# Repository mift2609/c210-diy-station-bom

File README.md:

# Checklist Belanja — Station Solder C210 DIY

Halaman checklist komponen untuk membangun station solder C210 (kartrid JBC C210) berbasis
Arduino Nano / ATmega328P + LMV358, ditujukan untuk service HP dan elektronik kecil.

- `index.html` — checklist interaktif: centang per komponen, harga bisa diedit, total otomatis,
  tombol salin daftar yang belum dibeli, dan link pencarian Shopee per komponen.
- `c210-station-belanja-uji.xlsx` — versi spreadsheet: daftar belanja, daftar upgrade,
  item off-PCB/gagang DIY, checklist uji terima, dan tabel kalibrasi suhu.
- `checklist.html` (kalau ada) — versi tanpa data harga Shopee.

## Estimasi biaya

| Bagian | Biaya |
|---|---|
| Komponen PCB wajib (otak + SMD + THT) | Rp159.500 |
| Off-PCB & gagang DIY (fab PCB, tip, soket, kabel, PSU, stand, enclosure) | Rp345.000 – Rp830.000 |
| Upgrade elektronik opsional (OPA2387, buck 5V, MOSFET ≥40V, earth tip, snubber) | +Rp87.000 |
| **Total** | **Rp504.500 – Rp989.500** (dengan upgrade: Rp587.500 – Rp1.072.500) |

## Varian gagang & rail (15 Nov 2026)

Satu board, satu colokan, gantian gagang:

- **C210 (12 V)** — rail dasar, kartrid ~2 ohm.
- **T210 / gagang 12 V** — lihat [`09-gantian-gagang.md`](09-gantian-gagang.md):
  autodetect gagang lewat ID pin (D10), 2 slot tip, firmware `firmware-gantian/`
  (v1.3-C210g, 24.412 byte).
- **T12 (24 V)** — lihat [`12-dual-rail-c210-t12.md`](12-dual-rail-c210-t12.md):
  PSU 36 V (terukur) -> buck 24 V (T12) + buck 12 V (C210) (buck input >= 50 V), dipilih **relay SPDT** yang
  dikendalikan D2; rail ikut profil tip otomatis. Firmware `firmware-dualrail/`
  (v1.3-dual, 24.570 byte). Wajib untuk rail 24 V: MOSFET >= 40 V, 5 V dari buck,
  sekring ikut R kartrid.

Tabel daya tip: C210 ~2 ohm -> 12 V = 72 W (24 V = 288 W, jangan);
T12 ~8 ohm -> 12 V = 18 W, 24 V = 72 W.

## Angka sekring & PSU: ukur R kartrid dulu

Doc lama memakai 8,5 ohm / ~1,4 A (angka tip T12). Rumus: `I = 12 / R`.

| R kartrid | Arus puncak @12 V | Sekring | PSU/rail |
|---|---|---|---|
| ~2 ohm (C210) | ~6,0 A | 8 A | >=8 A |
| ~2,5-3 ohm | ~4,0-4,8 A | 6,3-8 A | >=6 A |
| ~8 ohm (T12) | ~1,5 A | 3 A fast | >=3 A (lemah di 12 V) |

## Sebelum dipakai menyolder board HP

1. PSU harus **SELV/floating** — jangan pakai adaptor atau charger yang outputnya terhubung ke earth.
2. Sambungkan **kabel earth dari soket kartrid ke chassis** lalu ke PE. Ukur: tip-ke-earth < 2 Ω, kebocoran < 2 mV.
3. Kalibrasi suhu di 250/300/350 °C dengan thermocouple meter — target error < ±20 °C.
4. Uji fail-safe: cabut kartrid / satu kabel termokopel saat heater ON, daya harus terputus.
5. Kalau OPA2387 dipasang menggantikan LMV358, kalibrasi wajib diulang.

Catatan: seluruh angka harga adalah estimasi snapshot dan perlu dicek ulang saat membeli.

## Catatan gerber (penting)

File gerber asli yang beredar untuk board ini punya **cacat ekspor**: layer solder
mask (`F_Mask`/`B_Mask`) hanya memuat 56 bukaan untuk pad through-hole dan mounting
hole, sedangkan **pad SMD tidak punya bukaan sama sekali** (F_Cu punya 209 pad,
F_Mask hanya 56 objek; pad SMD terlihat tertutup mask pada render). Preview desainer
sendiri menunjukkan pad SMD terbuka, jadi ini murni cacat ekspor, bukan salah desain.

Kalau diorder apa adanya, pad SMD akan tertutup solder mask dan tidak bisa disolder.
Dua jalan keluar: minta desainer ekspor ulang gerber, atau pakai versi perbaikan
(mask di-generate ulang dari copper: bukaan THT dipertahankan + bukaan pad SMD
ditambahkan dengan ekspansi 0,1 mm, via tetap tertutup).

## Live

Checklist interaktif: https://mift2609.github.io/c210-diy-station-bom/

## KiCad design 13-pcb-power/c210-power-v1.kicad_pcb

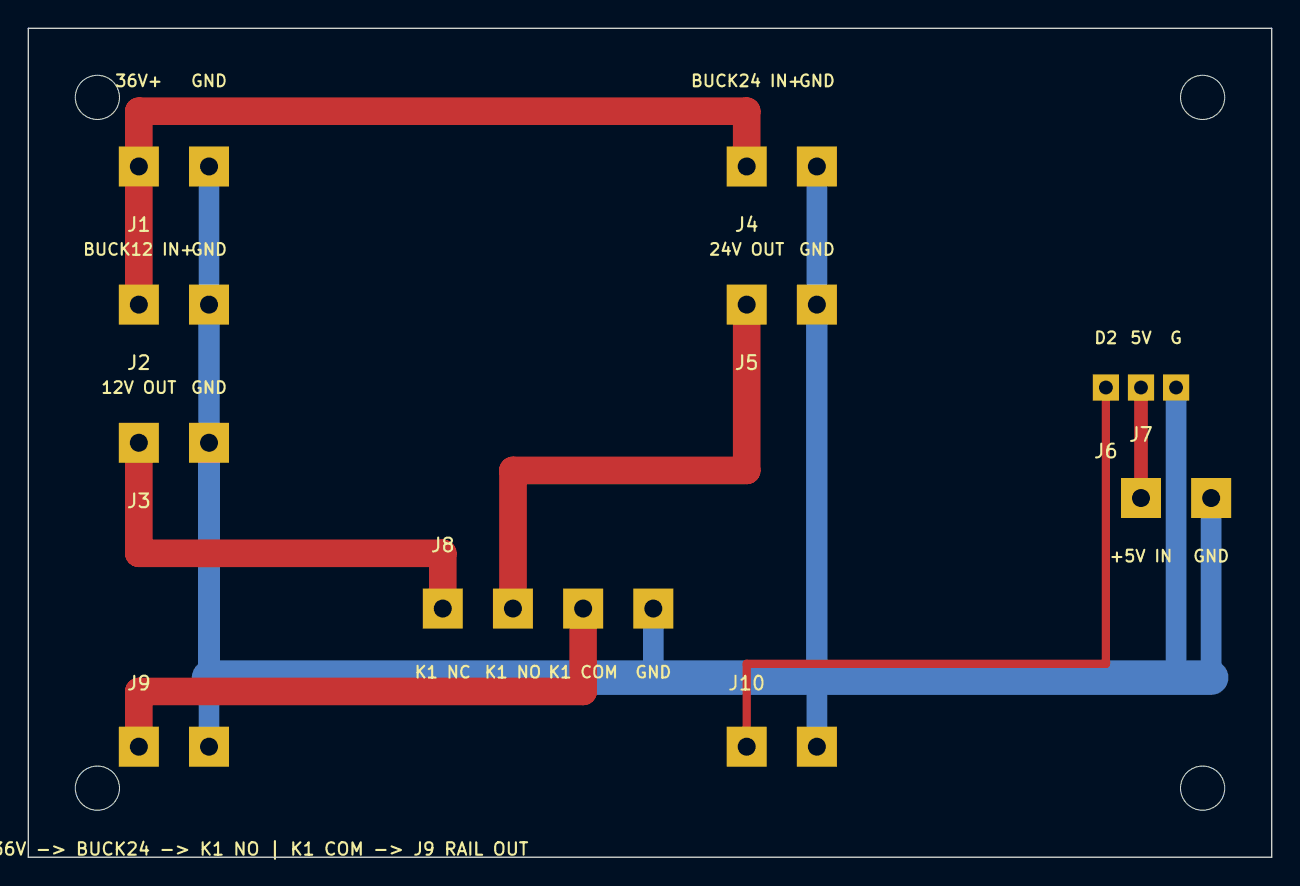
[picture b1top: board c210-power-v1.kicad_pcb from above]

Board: 2 copper layers, 90.0 x 60.0 mm, 14 parts (0 on the bottom side), 7 nets.

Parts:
H: M3; MountingHole_M3
H#2, H#3, H#4: M3; MountingHole_M3
J1, J2, J3, J4, J5, J7, J9, J10: conn; TerminalBlock_2x5.08mm
J6: conn; TerminalBlock_3x2.54mm
J8: conn; TerminalBlock_4x5.08mm

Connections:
CTRL_D2: J6.1, J10.1
GND: J1.2, J2.2, J3.2, J4.2, J5.2, J6.3, J7.2, J8.4, J9.2, J10.2
V5: J6.2, J7.1
V12: J3.1, J8.1
V24: J5.1, J8.2
V36: J1.1, J2.1, J4.1
VRAIL: J8.3, J9.1
